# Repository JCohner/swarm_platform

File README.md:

# Swarm Robotic Platform
### Josh Cohen

## Intro
With the goal of making decentralized, equitable, and sustainable systems, swarm robotic systems seem like a promising framework. Inspired by the success of the open source hardware community over the past 10 years and works like the [swarmbot: Jasmine](http://www.swarmrobot.org/), I hope to attempt to design my own low cost platform that can help propel swarm robotics into the real world. 

## TI CC1310
This is the [micro-conrtoller](http://www.ti.com/product/CC1310) we are using due to its small profile, low power consumption, and integrated RF capabilities. This board is currently interfacing with a [Pololu Zumo](https://www.pololu.com/product/2508) robot through a custom connector board.    

## Current Work
* Working "Firefly Synchronicity" inspired biosynchronicity algorithm that multiplexes time domain such that all robots can communicate within a given time period (\~1 second)
* 2 Working PCB Implementations:
	* Interface to Zumo Robot and CC13310 Launchpad XL
	* From scrath PCB for the CC1310 with working integrated PCB RF Antena that also serves as chassis for a diff drive robot
* Working line following robot that communcites based on the "Bayesian Particle" control laws researched by Ana Pervan and the Murphy lab
	* bit wise state machine to handle state transitions between every encountered intersection

## Directory Structure
* cc1310_code
	code running on the CC1310, controls zumo, implements RF synchronicity algorithm. See directory for more information
* listener
	* code that runs on "Hub" zumo, intercepts all TX'd messages from the zumo cc1310s and interperts the packets to be transmitted on via serial to the host computer, must also be used to communicate to zumos that start|stop them running or change their policies.  
* doc
	documentation relating to the Zumo, CC1310, and other components in this design
* eagle_files
	all PCB related documents
* scripts
	* a script to interpret and graph outputs of the ADC reads from the IR color sensors 
	* small c files in which we can test the bitwise state machine
* interface
	* hub.py is run to open the gui that lets you control the robots and collect data
* stls 
	* holds stl files for which the CAD can be found at [here](https://cad.onshape.com/documents?column=modifiedAt&nodeId=bd4b57b4a59c5991dd655b93&resourceType=folder&sortOrder=desc)

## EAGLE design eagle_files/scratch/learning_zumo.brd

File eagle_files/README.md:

##Board 2.0
Switched LM1117 voltage regs to constant output, 1 5v reg and one 3.3v output

## Board 1.0
Needs LM1117 to be adjustable

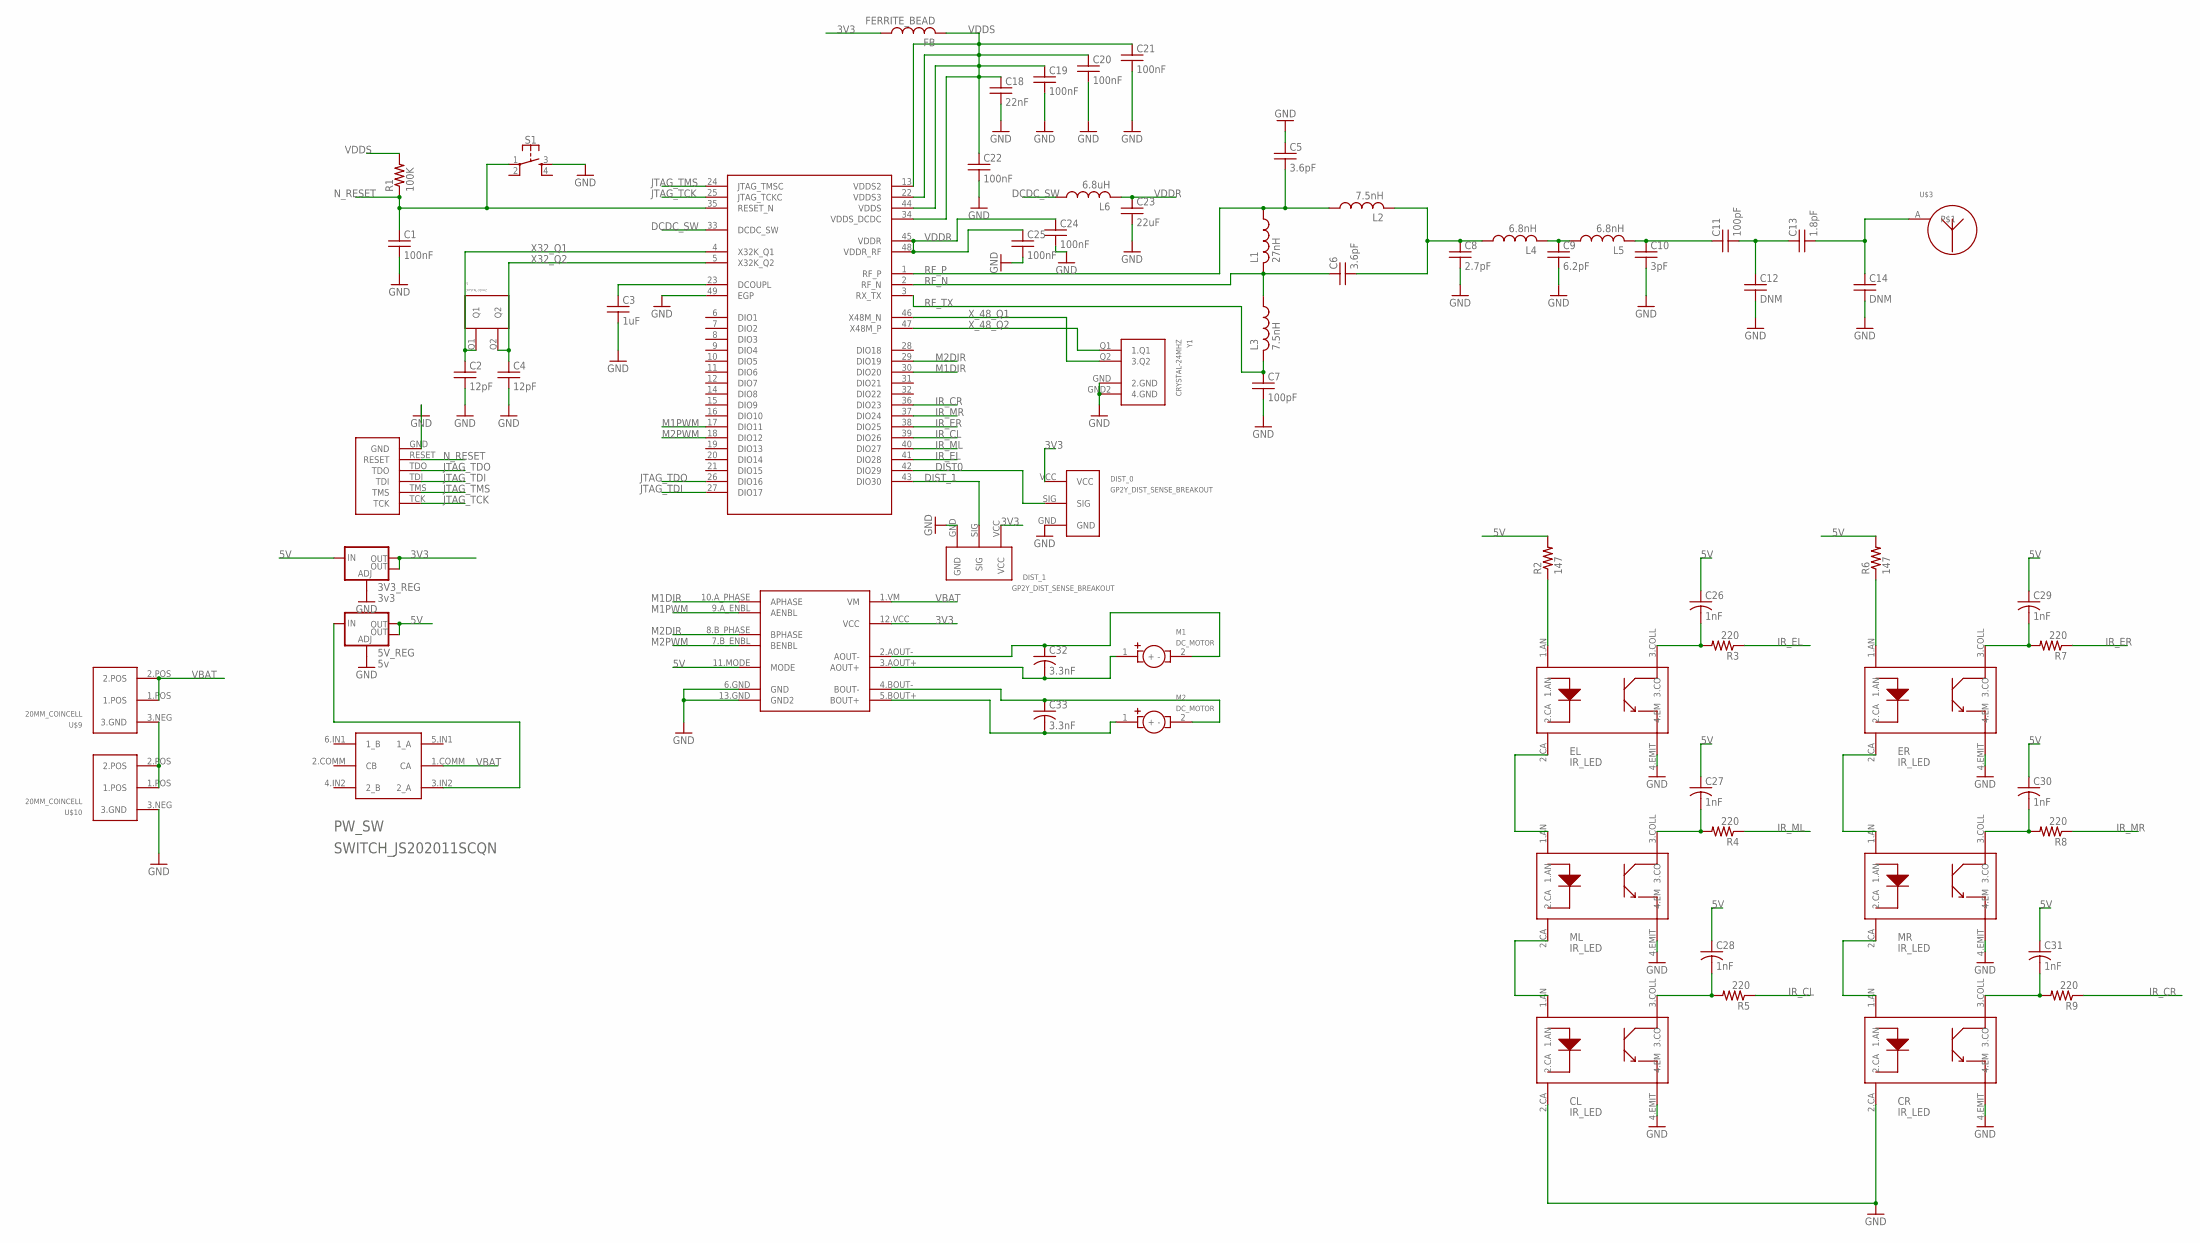
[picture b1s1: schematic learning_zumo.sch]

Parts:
3V3_REG: 3v3; NU32V7_SOT223
5V_REG: 5v; NU32V7_SOT223
C1, C19, C20, C21, C22, C24, C25: 100nF; C0402_US
C2, C4: 12pF; C0402_US
C3: 1uF; C0402_US
C5, C6: 3.6pF; C0402_US
C7, C11: 100pF; C0402_US
C8: 2.7pF; C0402_US
C9: 6.2pF; C0402_US
C10: 3pF; C0402_US
C12, C14: DNM; C0402_US
C13: 1.8pF; C0402_US
C18: 22nF; C0402_US
C23: 22uF; C0402_US
C26, C27, C28, C29, C30, C31: 1nF; C0805
C32, C33: 3.3nF; C0805
CL: IR_LED
CR: IR_LED
DEBUG_HEADER: DEBUG_BREAKOUT
DIST_0, DIST_1: GP2Y_DIST_SENSE_BREAKOUT; 1X03
DRV8835: DRV8835DRV8835; DRV8835
EL: IR_LED
ER: IR_LED
FB: FERRITE_BEAD
L1: 27nH; L0402_US
L2, L3: 7.5nH; L0402_US
L4, L5: 6.8nH; L0402_US
L6: 6.8uH; R0805
M1, M2: DC_MOTOR; 1X02
ML: IR_LED
MR: IR_LED
PW_SW: SWITCH_JS202011SCQN
R1: 100K; R0402_US
R2, R6: 147; R0805
R3, R4, R5, R7, R8, R9: 220; R0805
S1: MOMENTARY-SWITCH-SPST-2-SMD-4.6X2.8MM; TACTILE_SWITCH_SMD_4.6X2.8MM
U$1: CC1310; QFN50P700X700X100-49N
U$3: ANTENNA
U$9, U$10: 20MM_COINCELL
Y1: CRYSTAL-24MHZ
Y2: CRYSTAL-32KHZ

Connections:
3V3: 3V3_REG.OUTPUT (OUT), 3V3_REG.VOUT (OUT), DIST_0.VCC, DIST_1.VCC, DRV8835.12.VCC (VCC), FB.P$1 (1)
5V: 3V3_REG.INPUT (IN), 5V_REG.OUTPUT (OUT), 5V_REG.VOUT (OUT), C26.1, C27.1, C28.1, C29.1, C30.1, C31.1, DRV8835.11.MODE (MODE), R2.2, R6.2
DCDC_SW: L6.1, U$1.33 (DCDC_SW)
DIST0: DIST_0.SIG, U$1.42 (DIO29)
DIST_1: DIST_1.SIG, U$1.43 (DIO30)
GND: 3V3_REG.GND (ADJ), 5V_REG.GND (ADJ), C1.2, C2.2, C3.2, C4.2, C5.1, C7.2, C8.2, C9.2, C10.2, C12.2, C14.2, C18.2, C19.2, C20.2, C21.2, C22.2, C23.2, C24.2, C25.2, CL.2.CA, CL.4.EMIT (4.EM), CR.2.CA, CR.4.EMIT (4.EM), DEBUG_HEADER.GND, DIST_0.GND, DIST_1.GND, DRV8835.6.GND (GND), DRV8835.13.GND (GND2), EL.4.EMIT (4.EM), ER.4.EMIT (4.EM), ML.4.EMIT (4.EM), MR.4.EMIT (4.EM), S1.3, U$1.49 (EGP), U$10.3.NEG (3.GND), Y1.GND (2.GND), Y1.GND2 (4.GND)
IR_CL: R5.1, U$1.39 (DIO26)
IR_CR: R9.1, U$1.36 (DIO23)
IR_EL: R3.1, U$1.41 (DIO28)
IR_ER: R7.1, U$1.38 (DIO25)
IR_ML: R4.1, U$1.40 (DIO27)
IR_MR: R8.1, U$1.37 (DIO24)
JTAG_TCK: DEBUG_HEADER.TCK, U$1.25 (JTAG_TCKC)
JTAG_TDI: DEBUG_HEADER.TDI, U$1.27 (DIO17)
JTAG_TDO: DEBUG_HEADER.TDO, U$1.26 (DIO16)
JTAG_TMS: DEBUG_HEADER.TMS, U$1.24 (JTAG_TMSC)
M1DIR: DRV8835.10.A_PHASE (APHASE), U$1.30 (DIO20)
M1PWM: DRV8835.9.A_ENBL (AENBL), U$1.17 (DIO11)
M2DIR: DRV8835.8.B_PHASE (BPHASE), U$1.29 (DIO19)
M2PWM: DRV8835.7.B_ENBL (BENBL), U$1.18 (DIO12)
unnamed: C3.1, U$1.23 (DCOUPL)
unnamed: C9.1, L4.P$2 (2), L5.P$1 (1)
unnamed: C10.1, C11.1, L5.P$2 (2)
unnamed: 5V_REG.INPUT (IN), PW_SW.3.IN2 (2_A)
unnamed: U$9.3.NEG (3.GND), U$10.1.POS, U$10.2.POS
unnamed: C11.2, C12.1, C13.1
unnamed: C13.2, C14.1, U$3.A
unnamed: C6.2, C8.1, L2.P$2 (2), L4.P$1 (1)
unnamed: ER.1.AN, R6.1
unnamed: EL.1.AN, R2.1
unnamed: C26.2, EL.3.COLL (3.CO), R3.2
unnamed: EL.2.CA, ML.1.AN
unnamed: CL.1.AN, ML.2.CA
unnamed: C27.2, ML.3.COLL (3.CO), R4.2
unnamed: C33.2, DRV8835.5.BOUT+ (BOUT+), M2.1 (+)
unnamed: C33.1, DRV8835.4.BOUT- (BOUT-), M2.2 (-)
unnamed: C32.2, DRV8835.3.AOUT+ (AOUT+), M1.1 (+)
unnamed: C32.1, DRV8835.2.AOUT- (AOUT-), M1.2 (-)
unnamed: C28.2, CL.3.COLL (3.CO), R5.2
unnamed: C29.2, ER.3.COLL (3.CO), R7.2
unnamed: ER.2.CA, MR.1.AN
unnamed: CR.1.AN, MR.2.CA
unnamed: C30.2, MR.3.COLL (3.CO), R8.2
unnamed: C31.2, CR.3.COLL (3.CO), R9.2
N_RESET: C1.1, DEBUG_HEADER.RESET, R1.P$1 (1), S1.1, U$1.35 (RESET_N)
RF_N: C6.1, L1.P$2 (2), L3.P$1 (1), U$1.2 (RF_N)
RF_P: C5.2, L1.P$1 (1), L2.P$1 (1), U$1.1 (RF_P)
RF_TX: C7.1, L3.P$2 (2), U$1.3 (RX_TX)
VBAT: DRV8835.1.VM (VM), PW_SW.1.COMM (CA), U$9.1.POS, U$9.2.POS
VDDR: C23.1, C24.1, C25.1, L6.2, U$1.45 (VDDR), U$1.48 (VDDR_RF)
VDDS: C18.1, C19.1, C20.1, C21.1, C22.1, FB.P$2 (2), R1.P$2 (2), U$1.13 (VDDS2), U$1.22 (VDDS3), U$1.34 (VDDS_DCDC), U$1.44 (VDDS)
X32_Q1: C2.1, U$1.4 (X32K_Q1), Y2.Q1
X32_Q2: C4.1, U$1.5 (X32K_Q2), Y2.Q2
X_48_Q1: U$1.46 (X48M_N), Y1.Q2 (3.Q2)
X_48_Q2: U$1.47 (X48M_P), Y1.Q1 (1.Q1)

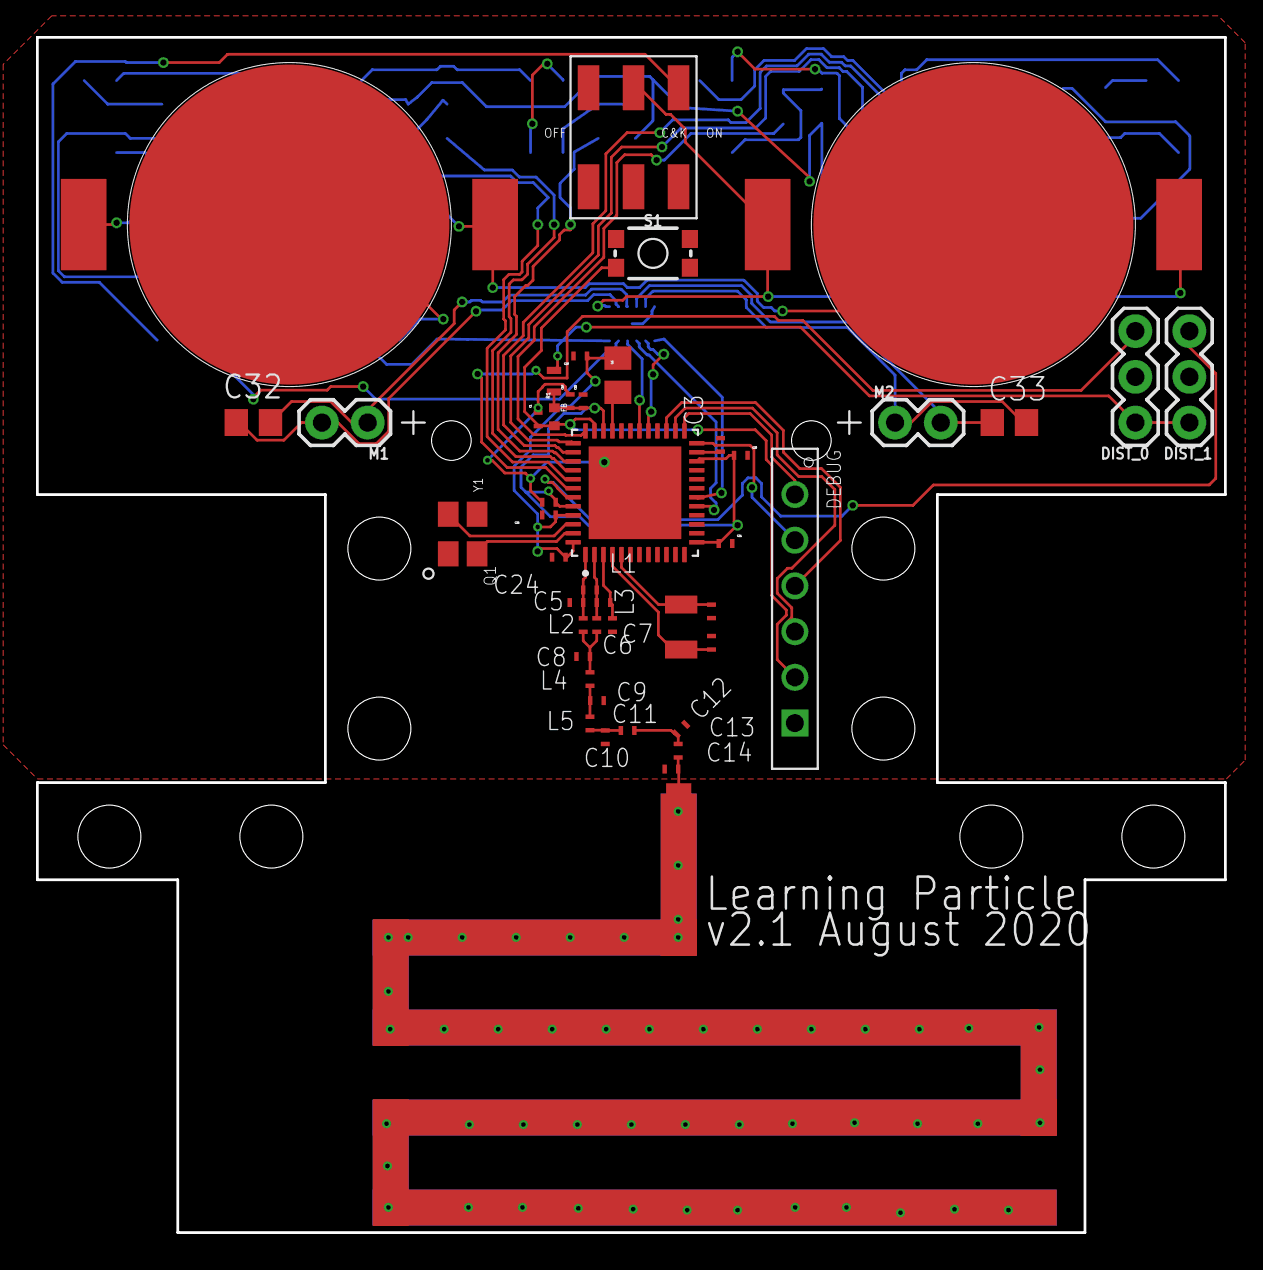
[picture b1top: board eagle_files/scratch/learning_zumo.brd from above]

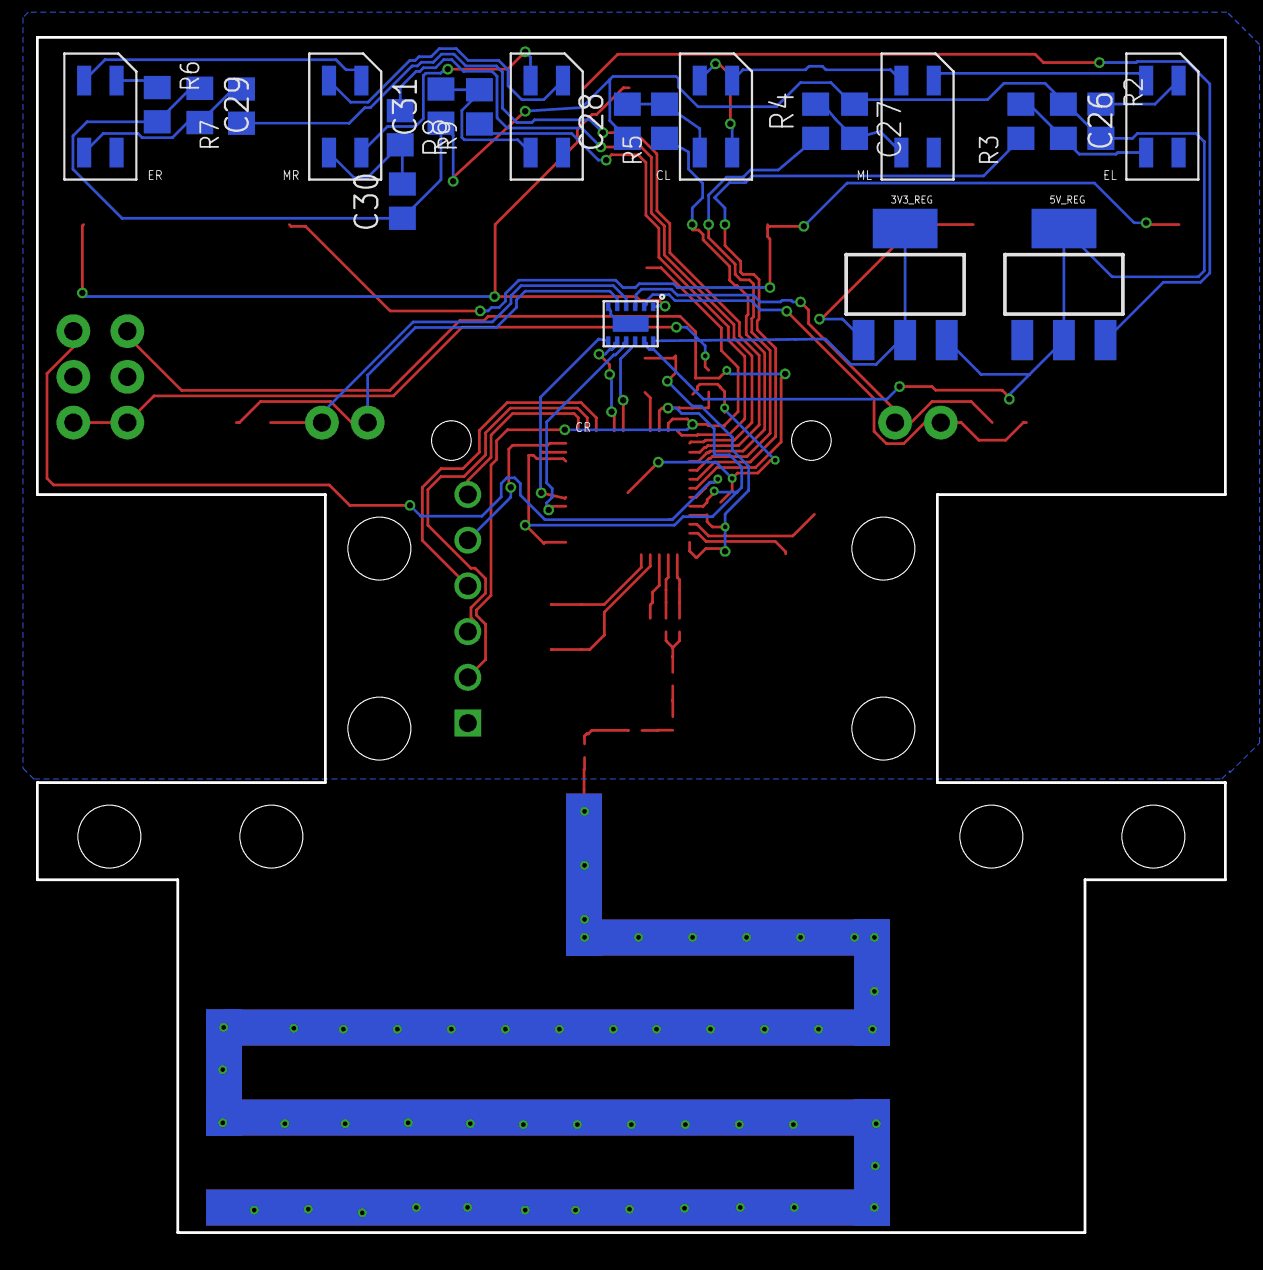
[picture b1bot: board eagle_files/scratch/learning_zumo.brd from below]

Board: 2 copper layers, 66.0 x 66.4 mm, 68 parts (23 on the bottom side), 55 nets.

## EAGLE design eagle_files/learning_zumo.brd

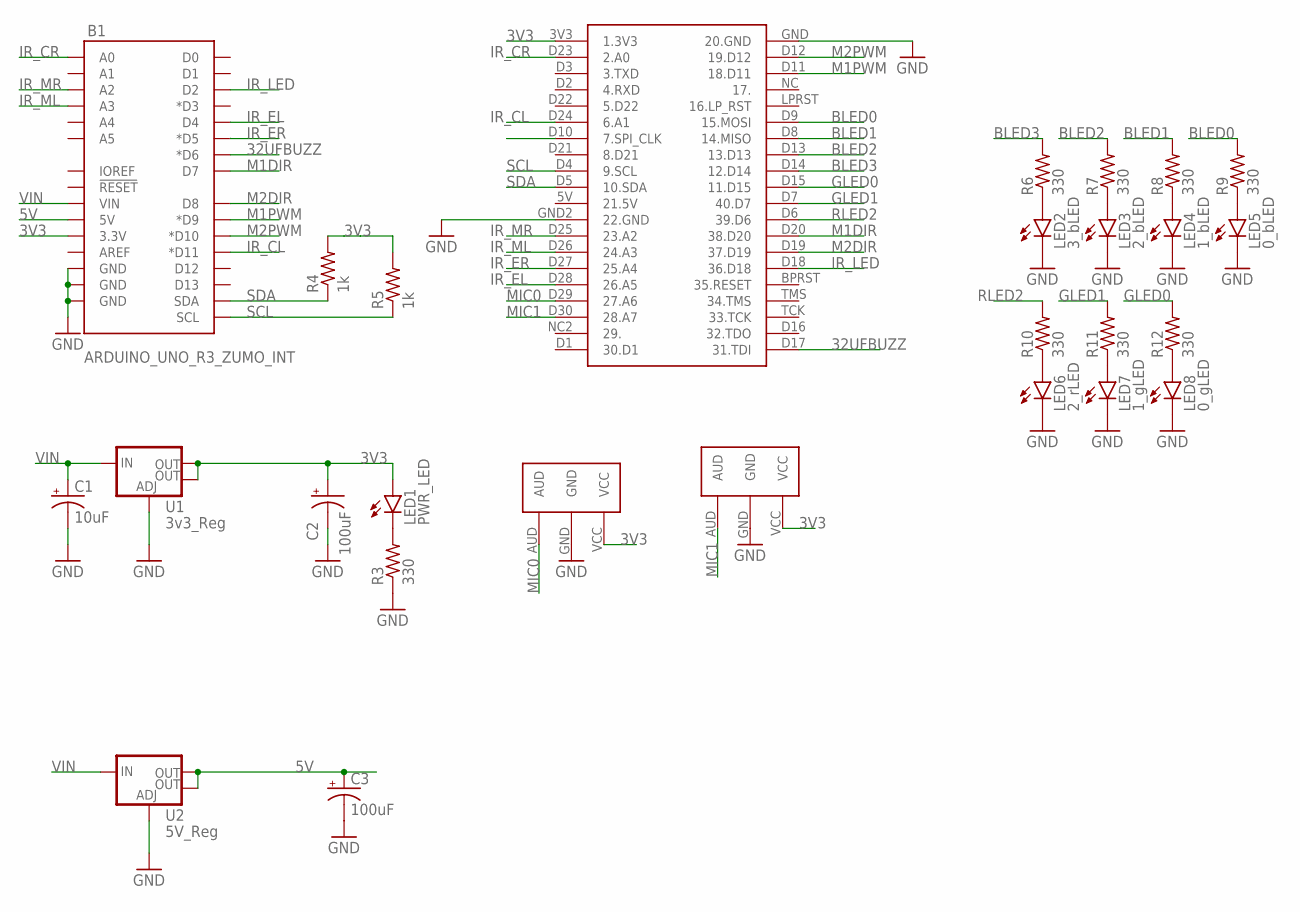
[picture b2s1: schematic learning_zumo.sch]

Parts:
B1: ARDUINO_UNO_R3_ZUMO_INT; UNO_R3_SHIELD_ICSP
C1: 10uF; E2,5-5
C2, C3: 100uF; E2,5-5
LED1: PWR_LED; LED5MM
LED2: 3_bLED; LED5MM
LED3: 2_bLED; LED5MM
LED4: 1_bLED; LED5MM
LED5: 0_bLED; LED5MM
LED6: 2_rLED; LED5MM
LED7: 1_gLED; LED5MM
LED8: 0_gLED; LED5MM
R3, R6, R7, R8, R9, R10, R11, R12: 330; 0207/10
R4, R5: 1k; 0207/10
U1: 3v3_Reg; NU32V7_SOT223
U2: 5V_Reg; NU32V7_SOT223
U$1: CC1310_INT
U$2, U$3: ANALOG_MIC

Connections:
3V3: B1.3.3V, C2.+, LED1.A, R4.2, R5.2, U1.OUTPUT (OUT), U1.VOUT (OUT), U$1.3V3 (1.3V3), U$2.VCC, U$3.VCC
5V: B1.5V, C3.+, U2.OUTPUT (OUT), U2.VOUT (OUT)
32UFBUZZ: B1.D6 (*D6), U$1.D17 (31.TDI)
BLED0: R9.2, U$1.D9 (15.MOSI)
BLED1: R8.2, U$1.D8 (14.MISO)
BLED2: R7.2, U$1.D13 (13.D13)
BLED3: R6.2, U$1.D14 (12.D14)
GLED0: R12.2, U$1.D15 (11.D15)
GLED1: R11.2, U$1.D7 (40.D7)
GND: B1.GND@0 (GND), B1.GND@1 (GND), B1.GND@2 (GND), C1.-, C2.-, C3.-, LED2.K (C), LED3.K (C), LED4.K (C), LED5.K (C), LED6.K (C), LED7.K (C), LED8.K (C), R3.1, U1.GND (ADJ), U2.GND (ADJ), U$1.GND (20.GND), U$1.GND2 (22.GND), U$2.GND, U$3.GND
IR_CL: B1.D11 (*D11), U$1.D24 (6.A1)
IR_CR: B1.A0, U$1.D23 (2.A0)
IR_EL: B1.D4, U$1.D28 (26.A5)
IR_ER: B1.D5 (*D5), U$1.D27 (25.A4)
IR_LED: B1.D2, U$1.D18 (36.D18)
IR_ML: B1.A3, U$1.D26 (24.A3)
IR_MR: B1.A2, U$1.D25 (23.A2)
M1DIR: B1.D7, U$1.D20 (38.D20)
M1PWM: B1.D9 (*D9), U$1.D11 (18.D11)
M2DIR: B1.D8, U$1.D19 (37.D19)
M2PWM: B1.D10 (*D10), U$1.D12 (19.D12)
MIC0: U$1.D29 (27.A6), U$2.AUD
MIC1: U$1.D30 (28.A7), U$3.AUD
unnamed: LED1.K (C), R3.2
unnamed: LED2.A, R6.1
unnamed: LED3.A, R7.1
unnamed: LED4.A, R8.1
unnamed: LED5.A, R9.1
unnamed: LED6.A, R10.1
unnamed: LED7.A, R11.1
unnamed: LED8.A, R12.1
RLED2: R10.2, U$1.D6 (39.D6)
SCL: B1.SCL, R5.1, U$1.D4 (9.SCL)
SDA: B1.SDA, R4.1, U$1.D5 (10.SDA)
VIN: B1.VIN, C1.+, U1.INPUT (IN), U2.INPUT (IN)

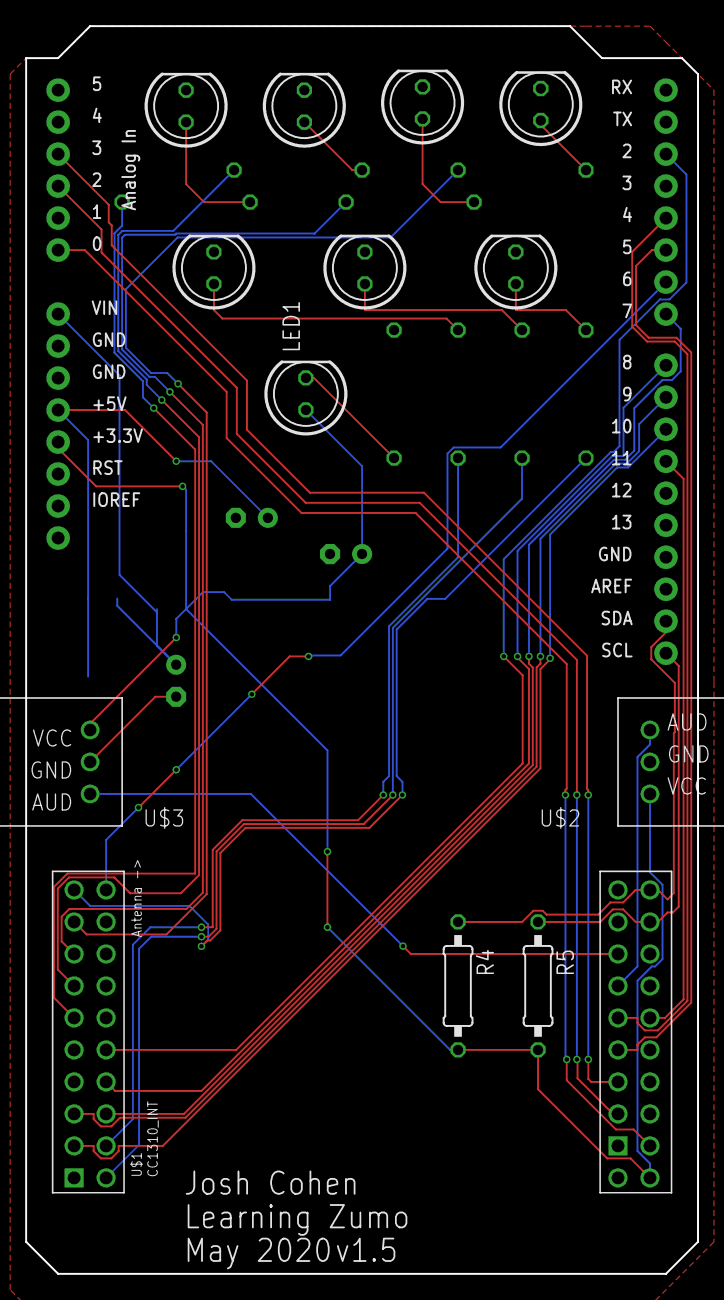
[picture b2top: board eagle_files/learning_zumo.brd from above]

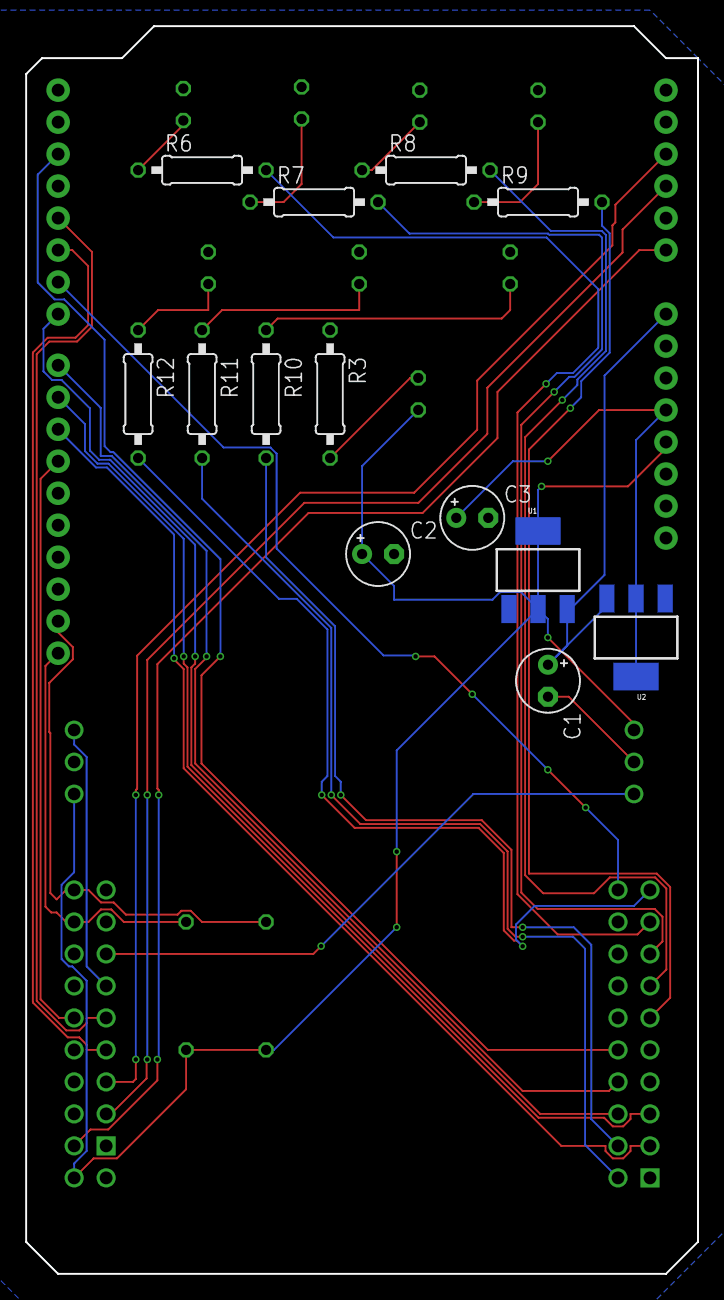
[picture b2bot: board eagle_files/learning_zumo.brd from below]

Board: 2 copper layers, 53.3 x 99.1 mm, 27 parts (13 on the bottom side), 35 nets.

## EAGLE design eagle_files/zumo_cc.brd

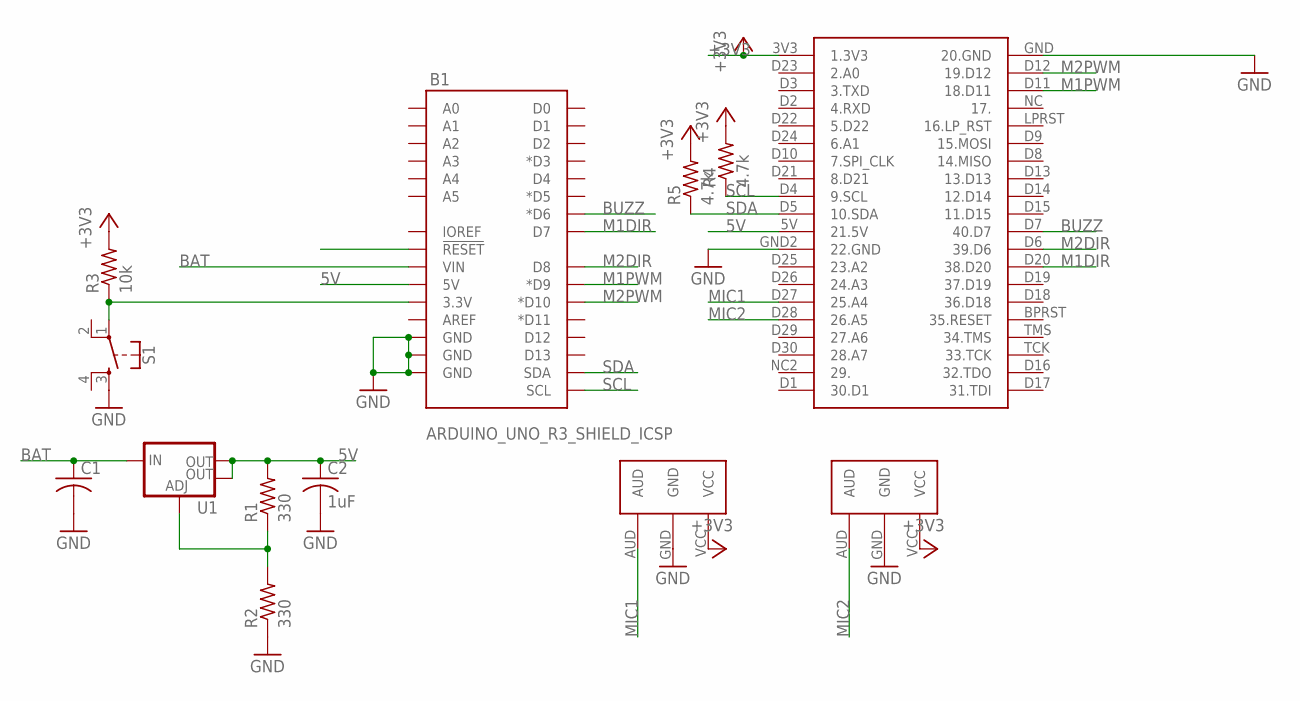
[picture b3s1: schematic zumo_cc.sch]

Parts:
B1: ARDUINO_UNO_R3_SHIELD_ICSP; UNO_R3_SHIELD_ICSP
C1, C2: 1uF; C0603
R1, R2: 330; R0603
R3: 10k; R0603
R4, R5: 4.7k; R0603
S1: MOMENTARY-SWITCH-SPST-2-SMD-5.2MM; TACTILE_SWITCH_SMD_5.2MM
U1: NU32V7_V_REG_LM1117SOT223; NU32V7_SOT223
U$1: CC1310_INT
U$2, U$3: ANALOG_MIC

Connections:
5V: B1.5V, C2.1, R1.2, U1.OUTPUT (OUT), U1.VOUT (OUT), U$1.5V (21.5V)
+3V3: R3.2, R4.2, R5.2, U$1.3V3 (1.3V3), U$2.VCC, U$3.VCC
BAT: B1.VIN, C1.1, U1.INPUT (IN)
BUZZ: B1.D6 (*D6), U$1.D7 (40.D7)
GND: B1.GND@0 (GND), B1.GND@1 (GND), B1.GND@2 (GND), C1.2, C2.2, R2.1, S1.3, U$1.GND (20.GND), U$1.GND2 (22.GND), U$2.GND, U$3.GND
M1DIR: B1.D7, U$1.D20 (38.D20)
M1PWM: B1.D9 (*D9), U$1.D11 (18.D11)
M2DIR: B1.D8, U$1.D6 (39.D6)
M2PWM: B1.D10 (*D10), U$1.D12 (19.D12)
MIC1: U$1.D27 (25.A4), U$2.AUD
MIC2: U$1.D28 (26.A5), U$3.AUD
unnamed: B1.3.3V, R3.1, S1.1
unnamed: R1.1, R2.2, U1.GND (ADJ)
SCL: B1.SCL, R4.1, U$1.D4 (9.SCL)
SDA: B1.SDA, R5.1, U$1.D5 (10.SDA)

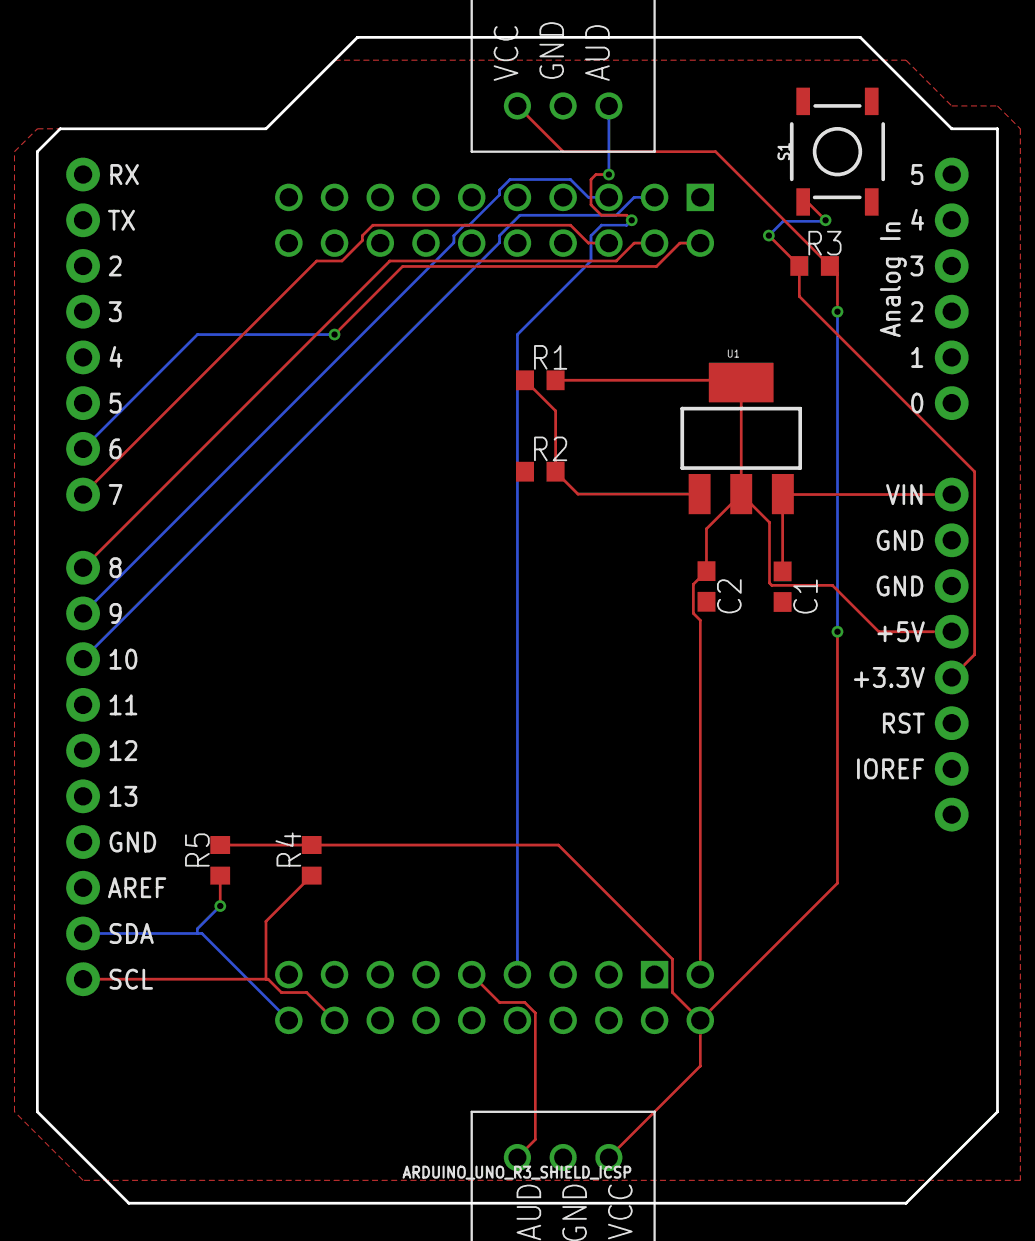
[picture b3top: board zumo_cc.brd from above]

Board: 2 copper layers, 53.3 x 64.8 mm, 13 parts (1 on the bottom side), 15 nets.

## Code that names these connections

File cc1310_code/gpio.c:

/*
 * gpio.c
 *
 *  Created on: Feb 21, 2020
 *      Author: jambox
 */

#include "gpio.h"
#include "zumo.h"

void InitGPIO(void)
{
    /* GPIO power */
    PRCMPeripheralRunEnable(PRCM_PERIPH_GPIO);
    PRCMLoadSet();
    while (!PRCMLoadGet());
    //configure on board LEDs
    IOCPortConfigureSet(CC1310_LAUNCHXL_PIN_GLED,IOC_PORT_GPIO, IOC_STD_OUTPUT);
    IOCPortConfigureSet(CC1310_LAUNCHXL_PIN_RLED,IOC_PORT_GPIO, IOC_STD_OUTPUT);
    GPIO_setOutputEnableDio(CC1310_LAUNCHXL_PIN_GLED, GPIO_OUTPUT_ENABLE);
    GPIO_setOutputEnableDio(CC1310_LAUNCHXL_PIN_RLED, GPIO_OUTPUT_ENABLE);

    //configure drive outputs
    IOCPortConfigureSet(M1_DIR,IOC_PORT_GPIO, IOC_STD_OUTPUT);
    IOCPortConfigureSet(M2_DIR,IOC_PORT_GPIO, IOC_STD_OUTPUT);
    GPIO_setOutputEnableDio(M1_DIR, GPIO_OUTPUT_ENABLE);
    GPIO_setOutputEnableDio(M2_DIR, GPIO_OUTPUT_ENABLE);

    // defining output leds
    IOCPortConfigureSet(BLED0, IOC_PORT_GPIO, IOC_STD_OUTPUT);
    GPIO_setOutputEnableDio(BLED0, GPIO_OUTPUT_ENABLE);

    IOCPortConfigureSet(BLED1, IOC_PORT_GPIO, IOC_STD_OUTPUT);
    GPIO_setOutputEnableDio(BLED1, GPIO_OUTPUT_ENABLE);

    IOCPortConfigureSet(BLED2, IOC_PORT_GPIO, IOC_STD_OUTPUT);
    GPIO_setOutputEnableDio(BLED2, GPIO_OUTPUT_ENABLE);

    IOCPortConfigureSet(BLED3, IOC_PORT_GPIO, IOC_STD_OUTPUT);
    GPIO_setOutputEnableDio(BLED3, GPIO_OUTPUT_ENABLE);
}

void SetAndWritePinHigh(uint32_t pin)
{
    IOCPortConfigureSet(pin, IOC_PORT_GPIO, IOC_STD_OUTPUT);
    GPIO_setOutputEnableDio(pin, GPIO_OUTPUT_ENABLE);
    GPIO_setDio(pin);
}

void SetGPIOPin(uint32_t pin)
{
    IOCPortConfigureSet(pin, IOC_PORT_GPIO, IOC_STD_OUTPUT);
    GPIO_setOutputEnableDio(pin, GPIO_OUTPUT_ENABLE);
}

void ClearPin(uint32_t pin)
{
    GPIO_clearDio(pin);
}

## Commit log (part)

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2020-02-26 working i2c!
2020-02-26 caight nasty bug
2020-02-26 Revert "Revert "caight nasty bug""
    This reverts commit 15b82bd76cc31b81697c6d9ede8fcac8df493eed.
2020-02-29 fixed broken i2c send
2020-03-01 initializing 2 pwm outputs and made function to set value
2020-03-01 abstraction to make sending motor commands easier
2020-03-02 middleware fro interfacing w rfc
2020-03-04 got RF Driver working
2020-03-13 resturcturting to take advantage of carrier sense
2020-03-15 reworking deeply
2020-03-16 semi working, overflowing the queue such that it never triggers writes. heabily correlated to the CS configuration called busyOp
2020-03-17 closer
2020-03-18 fixed queue filling issue
2020-03-18 best working bersion!
2020-03-19 ignoring all of CCS's overhead, hopefully we will move out of CCS one day...
2020-03-19 init read me push
2020-03-20 moving things around
2020-03-20 helpful doc
2020-03-20 details file structure
2020-03-31 changed project structure
2020-03-31 prototype of avergaing filter for 10 most recent time deltas
2020-04-01 caught int division bug
2020-04-06 papers on MIT cricket localization
2020-04-07 swithcing to devel
2020-04-09 non averaged semi working implementation
2020-04-14 liiited quickest switching tim to improve performance, non averaged imp working robustly
2020-04-14 custom ccs target config to program multiple CC1310s at once
2020-04-19 got a singleshot adc pin read working, the READADC() function doesnt quite work yet, but the singular read in init does
2020-04-25 added option to upload to single cc13x0 filled out default readme to give myself hints if i forget
2020-04-25 reflects single target config change
2020-04-26 debugged multiple read adc
2020-04-26 added delay() function
2020-05-10 added more utils for clock management
2020-05-10 more pin defs
2020-05-11 working IR drive to black
2020-05-11 moved constant definition to lower layer, defined global variables more effectively
2020-05-17 prototyping readline functionality
2020-05-17 added tics to second functionality
2020-05-17 minor power side revision, using fixedoutput versions of l1117 from now on, wont need any voltage but 3v3 and 5v can spare the 4 resistors and simplify board
2020-05-18 best pid effort so far (still bad)
2020-05-23 working line followinggit add zumo.*!
2020-05-25 named IR sensing pins
2020-05-25 further tuning control algo, fixed missed revision bug
2020-05-25 reflects most recent pcb changes
2020-05-28 jpgs of brd and schem for friends
2020-05-28 semi fixed averaging, still a bug that has to do with pre full buffer stuff
2020-06-01 prototype reading in barcode like data
2020-06-05 fiddling w ir sensing, trying turning emitters on 1 by 1
2020-06-07 taking 2 samples per sensor now instead of just 1
2020-06-07 added func to print large arrays over aurt
2020-06-08 1st implementation of py serial script, using to prototype barcode stuff rn
2020-06-09 stashing last of barcode, switching to a more state machine based interp
2020-06-10 going to clean up and refine poi detect. good proto framework though
2020-06-13 made a color tracking struct to make multi color tracking easier
2020-06-21 middleware for commanding open loop zumo control
2020-06-21 playing with intersection state machine management and openloop control
2020-06-22 merging with master
2020-06-23 low level state machine class abstraction
2020-06-23 repositioned this as high level abstraction that calls upon state_track, color_track, and zumo_move to operate, cleaned up a lot of code
2020-06-23 refining openloop control
2020-06-23 working actuation!
2020-06-23 removed dependency of zumo.h, clears up circular dependencies
2020-06-24 removed dependency on zumo.h and impleemnted a test_led feature
2020-06-24 added actuation and return flags as well as functionality to set and return return policy
2020-06-24 moved open loop control and execute polic logic here, implemented rotate function that calls motor actuation, added time based offset to openloop turn
2020-06-24 latest arena design, changed from maintaining state based on handedness of detected poi
2020-06-24 now takes filename as input
2020-06-25 added evalaute state function as well as a prev_return_flag to get more information out of state transitions, further implemented 'inc_xc_state()' which is a function that will handle state transitio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
2020-06-26 attempting to latch detection such that it only triggers once per color, not quite there yet
2020-06-26 latest arena design
2020-06-26 listnening hub that will print all RF messages to serial on computer for visualization
2020-06-26 printing utility and update arena 6
2020-06-30 printing out policy, state, return flag, and target
2020-06-30 greatly cleaned up main
2020-07-01 added graphite
2020-07-01 playing around with limiting comm range
2020-07-01 commented reflecting attempts to limit comm range
2020-07-01 attempting to implement biasing behavior
2020-07-02 added WriteRF(), takes a char array like WriteUART0(), sends message to listener cc1310
2020-07-02 reflecting change to simple grey
2020-07-02 added RF output tuned some open loop params
2020-07-02 replaced bias flag with actuation flag because they accomplish the same thing, cleared up language in zumo_moves
2020-07-02 incremented grey detect thresh
2020-07-03 added detection of white triangles on map, removed some reduntant purple detect code
2020-07-04 discovered most code actually was reduntant to the task, going to experiment with slowly adding more back
2020-07-04 cleaned up dependecies, reverted drive line back to more elegant solution
2020-07-04 added manage intersection to simplify and replace 'execute_policy()'
2020-07-05 made state transitions more robust by requiring color detcet flag must be seen before each intersection
2020-07-05 testing out some real time clock feautures and more advanced state machine
2020-07-06 most up to date arena
2020-07-10 experimenting with changing open loop params based on line following confidence
2020-07-10 refining communication paradigm to better facillitate multi bot communication, reintroducing CS capacities
2020-07-11 speeding up synched communication
2020-07-13 fine tuning and code cleanup, performance is great. improvements from here on out will involve adding info to the map for error catching
2020-07-13 changed carrier sense to carrer sniff such that we can have inter robot communication
2020-07-13 setup packing interpretation to be output overserial
2020-07-13 further cleanup, bio sync working well!
2020-07-13 this 'module' will manage communication related things. This will free the zump_rf module to focus on synchronization and data transmission, will this will handle populating the packets and interpret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
2020-07-13 ironed out last bugs that would let me use this at 1.27ms period
2020-07-13 open loop control is now called based on a timer interrupt
2020-07-13 prototyping packet interrpretation functionality
2020-07-15 fixed silly bug introduced by swithcing from RxSniff to plain RX
2020-07-15 messing with idle max and commented out some erroneous prints
2020-07-15 more elegant method of incorporating data from neighbor policy into our own state
2020-07-16 last cleanup pre tagging
2020-07-17 eagle libraries used in designs
2020-07-19 days worth of work, added a bunch of componenets to the libraries, gave the power considerations a first take, began implementing the board, implement motor driver circuitry
2020-07-22 moved all critical components to this single library
2020-07-22 figuring last details on antenna balun
2020-07-22 ignoring eagle artifcats
2020-07-22 finished up iteration 1 of the board!
2020-07-23 now representing state using stator and a cleaner transition system then the previously utilized but shift way
2020-07-23 switched to enum method of state rep
2020-07-23 added better logic to check near, it is a little opaque, but should be discernable if you track the bitwise operators
2020-07-24 pivoted to just piping the straight analog signal, interpolation to exact distance was not needed, saved a few ops
2020-07-24 added comment, found bug where read response doesnt work if i enable rssi append
2020-07-27 more complex map
2020-07-27 defined constant DIST_THRESH for distance sensing
2020-07-27 pulling up to most up to date
2020-07-28 stashing working solution for more elegant one :p
2020-07-28 now oscillates between branches as well as within!
2020-07-29 simple bit mirroring script, used in figuring out return path
2020-07-29 moved away from enumeration based defs
2020-07-29 changed our open loop function such that it can perform the correct masking and bitwise operations on the policy (with the newly expanded state and policy), added a helper to aid in this
2020-07-29 bom for v1.75 and v2.0 boards
2020-07-30 added caveat such that the 0b11 state with policy 0b11 will fast forward to merge with other states
2020-07-30 editted listener such that could interpret new included bit
2020-08-06 using async uart to act as listner hub but also send commands to our friends (fellow swarm bots)
2020-08-06 api to post messages
2020-08-06 comm now checks if the incoming message is addressed to itself, if so it treats the packet as a command packet that can update policy or trigger a start cond
2020-08-06 slightly tweaked targ thresh for new map, also where in xc state the targ would be detected
2020-08-06 changed an inductor comp
2020-08-07 2 main features: added ability to switch to new policy sent from hub
2020-08-07 removed accidental adds
2020-08-07 front end gui
2020-08-10 connected buttons to actual functionalities
2020-08-10 packet struct to make communication easier
2020-08-11 fixed up some silliniess, now properly splitting the timer (GPT1) into Timer_A and Timer_B using timerA for motor control, timerB for fixed rate actuation of radio
2020-08-11 moving from scripts to here, this will be the desktop interface into interacting with the swarm and deserves to be at the top level
2020-08-11 ignore python artifact files
2020-08-11 big change where we moved all sensing and driving commands to an interrupt timer
2020-08-12 to fit 2 byte robot ID had to increase the amount of bytes packed into packets
2020-08-12 added classful nature
2020-08-12 commented out debug print statements
2020-08-13 caught bug of sender id in comm packet being 8 bit instead of newly expanded 16 bit
2020-08-13 building out modularity of state machine system such that it is easy to switch between two map designs
2020-08-13 needed to shift transmitted packages to 32 bit encoding as well
2020-08-14 slowed down speed of rf interupt to something more reasonable to make it work better
2020-08-14 defined minimum idle time as well
2020-08-16 found insidious bug, used strtol instead of strtoul, which lead to truncation of full 32 bit entries to the 2s compliment format (present in IDs with first char being > 7)
2020-08-17 fixed grey values on new quartet copy paper
2020-08-17 found tough bug in updating policy, need to make sure we're back on line before updating
2020-08-18 broke out 'true random number generator periph'
2020-08-18 intialization for random num gen periph
2020-08-19 tool for analyzing efficacy of time multiplexing of biosynchronicity algorithm
2020-08-22 broke out side distance sensor
2020-08-22 caught bug where we were incorrectly writing successful neighbor policy (due to chaning packet struct)
2020-08-22 now incorporating side distance sensor reading into drive mechanics
2020-08-22 added doyxgen style (and general) comments, randomizedd starting policy, added some debug prints to main loop
2020-08-23 made code threadful such that we could read and write from serial port
2020-08-24 interpreter for data post collection
2020-08-24 rework of 'check_near' function that ensured only robots on the same segment could communicate
2020-08-26 added check near functionality for circ system
2020-08-26 added check distance function (not in use in this iteration) that will reverse if too close, right now functionality just stops the robot when it is too close
2020-08-26 added unique pol grabber per MAC address if we dont want to grab random ones
2020-08-27 updated to handle data coming back from circ maze
2020-08-28 reformated, left commented out functions for future implementation attempts
2020-08-28 tried to make target detect less permissive
2020-08-28 latest WORKING version of board and schematic
2020-08-28 added ability to set counts of open loop counter
2020-08-30 readme push
